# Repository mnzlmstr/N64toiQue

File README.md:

### What is this Project about ?

In the early 2000s Nintendo released a version of the N64 Console for the Chinese Market called the iQue Player. This Console is much looked after and increasingly hard to come by.
This is made worse by the fact that the inputs, such as the Buttons and the Joystick are hardwired to the Console. As my console began to wear down I sought a way to be able to connect a standart N64 controller to the console. As this was not done yet I created this repository to aid people seeking to do something similar in collecting all the scarce information in one place

### How far along is the Project ?

The current code is working as intended and I played through the first Dungeons of Legen of Zelda - Ocarina of Time without any problems. However the Project is still a mess of wires, and not all Buttons have been hooked up yet. I intend to create a PCB to mount everything back into the origin casing and upload the Eagle Files to this repository, as well as to create assembly instructions and maybe also upload precompiled binaries.

While the first PRB Revision appears to be working right now i will look into improving the PCB to allow <br/>
the User to see if everything is in owrking Order by incorporating LEDs in the PCB as well as a header for 
Programming, which as of right now has to be done beforehand.

### What Hardware is needed for the Project ?

The code is designed to be run on a ESP32 Microprocessor from Espressif running @ 240Mhz.

### What Software is needed to compile from source ?

The code was compiled using Arduino IDE and version 1.0.4 of the Arduino-ESP32 Core.
As Timing is very critical (a bit read from the controller takes only 4uS !) I decided to not bother with working around the compiler optimizations and decided to disable them alltogether. This means you will have to edit the `platform.txt` file to set optimization level to -O0.

### Will I need to perform manual changes ?

Yes you will have to edit the Pins used in the file `PinMappings.h` to match the Pins you wired everything up with. The Axis pins have to be connected to the correct Wires coming from the Joystick. For that is adviced to cut the Joystick cable in half and connect the X-Axis pins to the pins labeled 1 & 4 of the Joystick PCB and the Y-Axis pins to the pins labeled 5 & 6.

### Changelog:

13.04.2020:<br/>
	- moved source code to `src` folder<br/>
	- added precompiled binaries for Heltec WiFi LoRa 32 V2 to folder `bin`<br/>
	- added first PCB Files (untested, just ordered them today) <br/>
<br/>
15.05.2020: <br/>
	- PCB has been tested an appears to be working just fine<br/>
	- Add: Updater to be able to upload new firmware over HTTP hosted by ESP32
	- Add: precompiled binary for firebeetle-esp32
	- TODO: redesigning PCB to incorporate LEDs for user feedback as well as Programming Header<br/>
<br/>

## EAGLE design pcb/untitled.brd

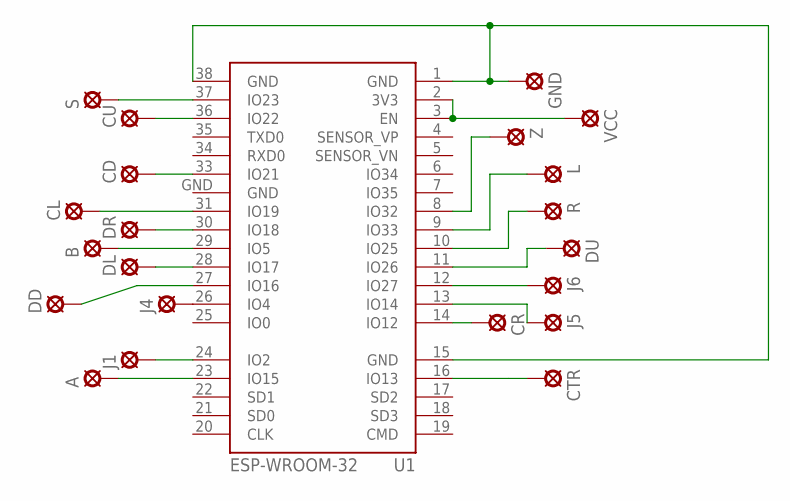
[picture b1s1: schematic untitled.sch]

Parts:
A: LSP13
B: LSP13
CD: LSP13
CL: LSP13
CR: LSP13
CTR: LSP13
CU: LSP13
DD: LSP13
DL: LSP13
DR: LSP13
DU: LSP13
GND: LSP13
J1, J4, J5, J6: LSP13
L: LSP13
R: LSP13
S: LSP13
U1: ESP-WROOM-32
VCC: LSP13
Z: LSP13

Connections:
GND: GND.MP, U1.1 (GND), U1.15 (GND), U1.38 (GND), U1.GND
unnamed: U1.8 (IO32), Z.MP
unnamed: U1.2 (3V3), U1.3 (EN), VCC.MP
unnamed: CTR.MP, U1.16 (IO13)
unnamed: A.MP, U1.23 (IO15)
unnamed: B.MP, U1.29 (IO5)
unnamed: S.MP, U1.37 (IO23)
unnamed: J4.MP, U1.26 (IO4)
unnamed: J1.MP, U1.24 (IO2)
unnamed: J6.MP, U1.12 (IO27)
unnamed: J5.MP, U1.13 (IO14)
unnamed: L.MP, U1.9 (IO33)
unnamed: R.MP, U1.10 (IO25)
unnamed: DU.MP, U1.11 (IO26)
unnamed: DD.MP, U1.27 (IO16)
unnamed: DL.MP, U1.28 (IO17)
unnamed: DR.MP, U1.30 (IO18)
unnamed: CU.MP, U1.36 (IO22)
unnamed: CD.MP, U1.33 (IO21)
unnamed: CL.MP, U1.31 (IO19)
unnamed: CR.MP, U1.14 (IO12)

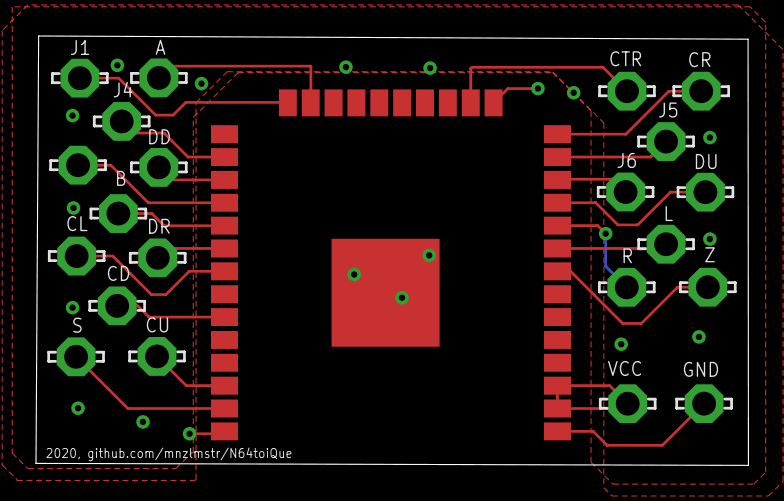
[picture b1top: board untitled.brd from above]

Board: 2 copper layers, 39.6 x 23.9 mm, 22 parts (0 on the bottom side), 21 nets.

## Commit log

2020-04-13 created src folder, included precompiled binaries
2020-04-13 deleted source files from root
2020-04-13 added newlines to readme
2020-04-13 Create LICENSE
2020-04-13 added PCB Layout
2020-05-16 fix: README typo
2020-05-16 add: precompiled binary for firebeetle-esp32, add: HTTPUpdate functionality

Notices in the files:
parts and their libraries:
esp32: Creative Commons Attribution-ShareAlike 4.0 International
